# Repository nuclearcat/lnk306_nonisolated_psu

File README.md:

# lnk306_nonisolated_psu
WARNING! This is an non-isolated power supply, so even the DC output will have a dangerous mains potential.
Do not use it unless you know the difference between isolated or non-isolated power supply.

TBD: Dont use current version yet, small mistake in BOM for connectors, will fix it soon

My goal was to obtain a DC-DC supply with a very wide operating voltage range. 
On tests with 5v output, this power supply provides enough voltage for esp32 starting from 20v input voltage (DC)

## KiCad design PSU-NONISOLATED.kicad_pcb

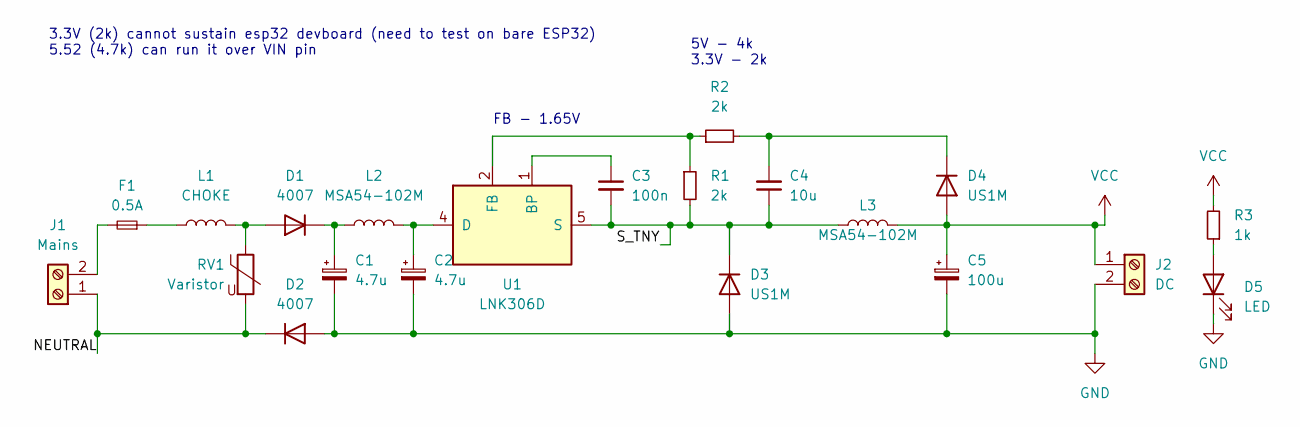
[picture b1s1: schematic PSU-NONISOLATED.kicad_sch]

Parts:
C1, C2: 4.7u; CP_Radial_D8.0mm_P3.50mm; LCSC PN C112471
C3: 100n; C_0603_1608Metric; LCSC PN C77055
C4: 10u; C_1206_3216Metric; LCSC PN C13585
C5: 100u; CP_Radial_D6.3mm_P2.50mm; LCSC PN C19504
D1, D2: 4007; D_SOD-123F; LCSC PN C64898
D3, D4: US1M; D_SMA; LCSC PN C412437
D5: LED; LED_0603_1608Metric; LCSC PN C2286
F1: 0.5A; R_Axial_DIN0204_L3.6mm_D1.6mm_P7.62mm_Horizontal
J1: Mains; TerminalBlock_Altech_AK300-2_P5.00mm; LCSC PN C72334
J2: DC; TerminalBlock_Altech_AK300-2_P5.00mm; LCSC PN C72334
L1: CHOKE; R_Axial_DIN0204_L3.6mm_D1.6mm_P7.62mm_Horizontal
L2, L3: MSA54-102M; L_TracoPower_TCK-047_5.2x5.8mm; LCSC PN C396419
R1, R2: 2k; R_0603_1608Metric; LCSC PN C22975
R3: 1k; R_0603_1608Metric; LCSC PN C21190
RV1: Varistor; RV_Disc_D9mm_W6.1mm_P5mm; LCSC PN C111187
U1: LNK306D; PowerIntegrations_SO-8C; LCSC PN C34318

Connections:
/NEUTRAL: D2.1 (K), J1.1, RV1.2
/S_TNY: C3.2, C4.1, D3.1 (K), L3.1, R1.2, U1.5 (S), U1.6 (S), U1.7 (S), U1.8 (S)
GND: C1.2, C2.2, C5.2, D2.2 (A), D3.2 (A), D5.1 (K), J2.2
unnamed: C3.1, U1.1 (BP)
unnamed: C4.2, D4.1 (K), R2.2
unnamed: C1.1, D1.1 (K), L2.1
unnamed: D1.2 (A), L1.2, RV1.1
unnamed: D5.2 (A), R3.1
unnamed: F1.1, L1.1
unnamed: F1.2, J1.2
unnamed: C2.1, L2.2, U1.4 (D)
unnamed: R1.1, R2.1, U1.2 (FB)
VCC: C5.1, D4.2 (A), J2.1, L3.2, R3.2

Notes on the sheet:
3.3V (2k) cannot sustain esp32 devboard (need to test on bare ESP32) 5.52 (4.7k) can run it over VIN pin
FB - 1.65V
5V - 4k 3.3V - 2k

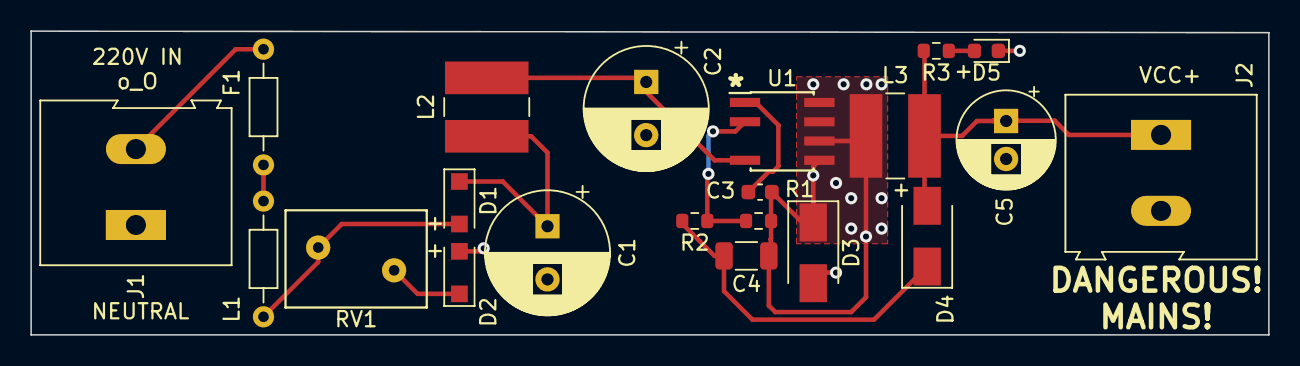
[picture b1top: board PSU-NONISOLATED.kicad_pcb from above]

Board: 2 copper layers, 81.5 x 20.0 mm, 21 parts (0 on the bottom side), 13 nets.

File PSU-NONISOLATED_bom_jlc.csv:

"Comment","Designator","Footprint","LCSC Part #"
"4.7u","C1,C2","CP_Radial_D8.0mm_P3.50mm","C112471"
"100n","C3","C_0603_1608Metric","C77055"
"10u","C4","C_1206_3216Metric","C13585"
"100u","C5","CP_Radial_D6.3mm_P2.50mm","C19504"
"4007","D1,D2","D_SOD-123F","C64898"
"US1M","D3,D4","D_SMA","C412437"
"LED","D5","LED_0603_1608Metric","C2286"
"Mains","J1","TerminalBlock_Altech_AK300-2_P5.00mm","C72334"
"DC","J2","TerminalBlock_Altech_AK300-2_P5.00mm","C72334"
"MSA54-102M","L2,L3","L_TracoPower_TCK-047_5.2x5.8mm","C396419"
"2k","R1,R2","R_0603_1608Metric","C22975"
"1k","R3","R_0603_1608Metric","C21190"
"Varistor","RV1","RV_Disc_D9mm_W6.1mm_P5mm","C111187"
"LNK306D","U1","PowerIntegrations_SO-8C","C34318"

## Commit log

2021-12-29 Working (tested) version
2021-12-29 Add schematics PDF and gerbers
2021-12-29 Description and some silkscreen for v2
2021-12-29 Add BOM and CPL
2022-01-09 Create LICENSE
